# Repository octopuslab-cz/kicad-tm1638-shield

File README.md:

# kicad-tm1638-shield
display and keyboard shield for octopusLAB ESP32board

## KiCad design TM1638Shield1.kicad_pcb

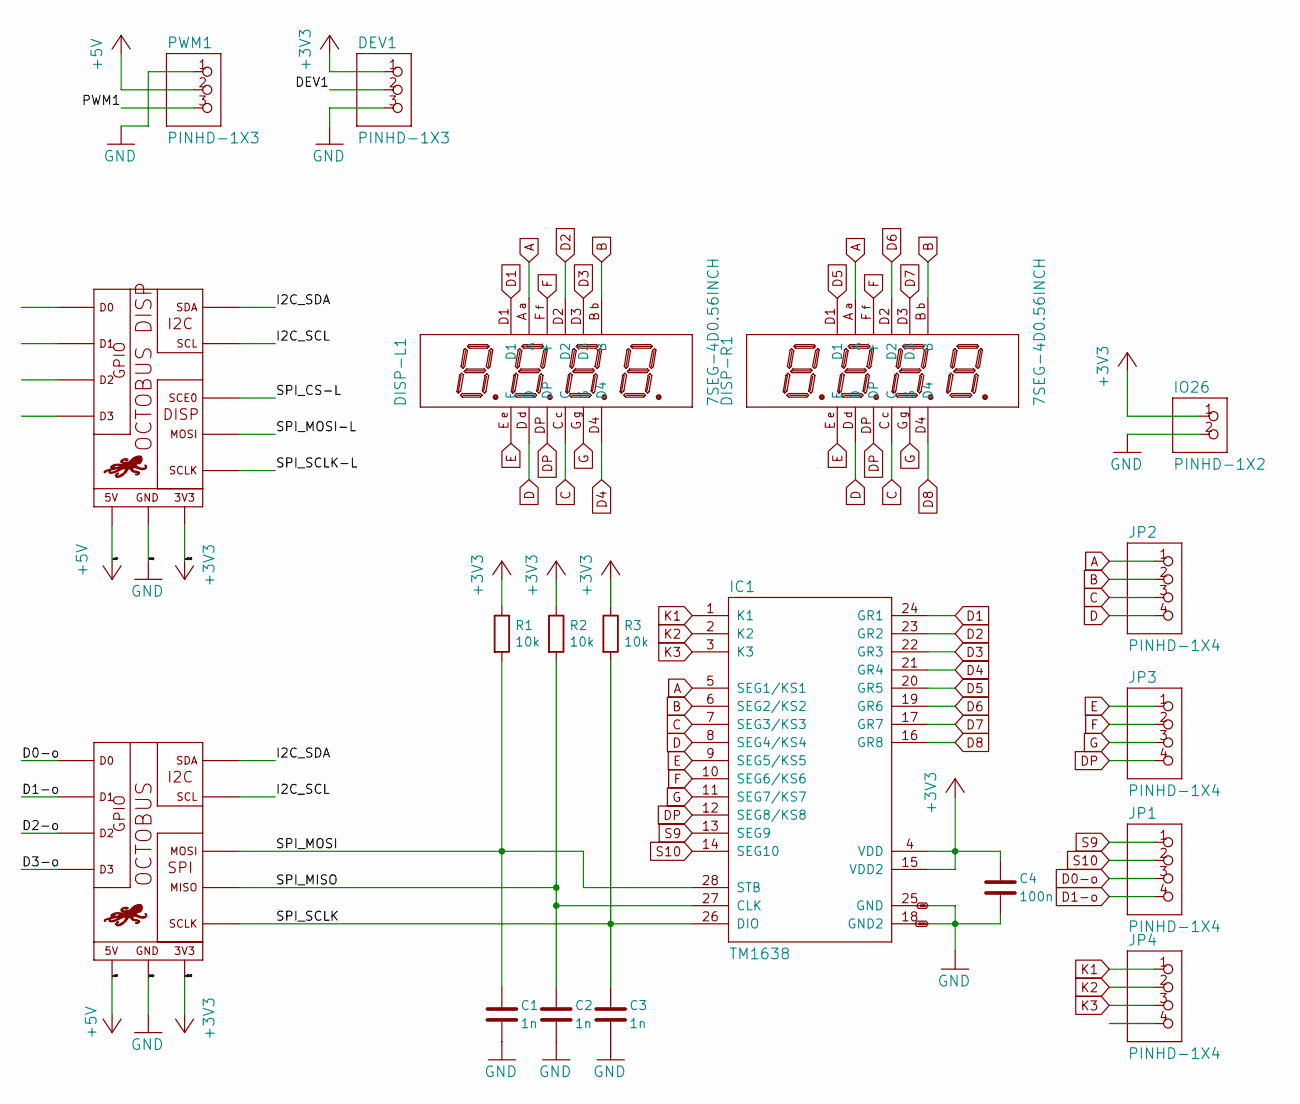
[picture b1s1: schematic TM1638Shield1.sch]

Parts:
C1, C2, C3: 1n; C_0805_2012Metric
C4: 100n; C_0805_2012Metric
DEV1: PINHD-1X3; 1X03
DISP-L1: 7SEG-4D0.56INCH; BQ-MB14RD
DISP-R1: 7SEG-4D0.56INCH; BQ-MB14RD
IC1: TM1638; SOP28
IO26: PINHD-1X2; 1X02
JP1, JP2, JP3, JP4: PINHD-1X4; 1X04
PWM1: PINHD-1X3; 1X03
R1, R2, R3: 10k; R_0805_2012Metric
U$1: OCTOBUSFULL; OCTOBUS
U$4: OCTOBUS_DISP

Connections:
+3V3: C4.1, DEV1.1, IC1.4 (VDD), IC1.15 (VDD2), IO26.1, R1.1, R2.1, R3.1, U$1.3V3, U$1.3V3_2 (3V3), U$1.3V3_AUX (3V3), U$4.3V3, U$4.3V3_2 (3V3)
+5V: PWM1.2, U$1.5V, U$1.5V_AUX (5V), U$4.5V
/D2-o: U$1.D2, U$1.D2_AUX (D2)
/D3-o: U$1.D3, U$1.D3_AUX (D3)
/DEV1: DEV1.2
/I2C_SCL: U$1.I2C_SCL (SCL), U$4.I2C_SCL (SCL)
/I2C_SDA: U$1.I2C_SDA (SDA), U$4.I2C_SDA (SDA)
/PWM1: PWM1.3
/SPI_CS-L: U$4.SPI_SCE0 (SCE0)
/SPI_MISO: C2.1, IC1.27 (CLK), R2.2, U$1.SPI_MISO (MISO)
/SPI_MOSI: C1.1, IC1.28 (STB), R1.2, U$1.SPI_MOSI (MOSI)
/SPI_MOSI-L: U$4.SPI_MOSI (MOSI)
/SPI_SCLK: C3.1, IC1.26 (DIO), R3.2, U$1.SPI_SCLK (SCLK)
/SPI_SCLK-L: U$4.SPI_SCLK (SCLK)
A: DISP-L1.A, DISP-R1.A, IC1.5 (SEG1/KS1), JP2.1
B: DISP-L1.B, DISP-R1.B, IC1.6 (SEG2/KS2), JP2.2
C: DISP-L1.C, DISP-R1.C, IC1.7 (SEG3/KS3), JP2.3
D: DISP-L1.D, DISP-R1.D, IC1.8 (SEG4/KS4), JP2.4
D0-o: JP1.3, U$1.D0, U$1.D0_AUX (D0)
D1: DISP-L1.D1, IC1.24 (GR1)
D1-o: JP1.4, U$1.D1, U$1.D1_AUX (D1)
D2: DISP-L1.D2, IC1.23 (GR2)
D3: DISP-L1.D3, IC1.22 (GR3)
D4: DISP-L1.D4, IC1.21 (GR4)
D5: DISP-R1.D1, IC1.20 (GR5)
D6: DISP-R1.D2, IC1.19 (GR6)
D7: DISP-R1.D3, IC1.17 (GR7)
D8: DISP-R1.D4, IC1.16 (GR8)
DP: DISP-L1.DP, DISP-R1.DP, IC1.12 (SEG8/KS8), JP3.4
E: DISP-L1.E, DISP-R1.E, IC1.9 (SEG5/KS5), JP3.1
F: DISP-L1.F, DISP-R1.F, IC1.10 (SEG6/KS6), JP3.2
G: DISP-L1.G, DISP-R1.G, IC1.11 (SEG7/KS7), JP3.3
GND: C1.2, C2.2, C3.2, C4.2, DEV1.3, IC1.18 (GND2), IC1.25 (GND), IO26.2, PWM1.1, U$1.GND, U$1.GND_2 (GND), U$1.GND_AUX (GND), U$4.GND, U$4.GND_2 (GND)
K1: IC1.1 (K1), JP4.1
K2: IC1.2 (K2), JP4.2
K3: IC1.3 (K3), JP4.3
S9: IC1.13 (SEG9), JP1.1
S10: IC1.14 (SEG10), JP1.2

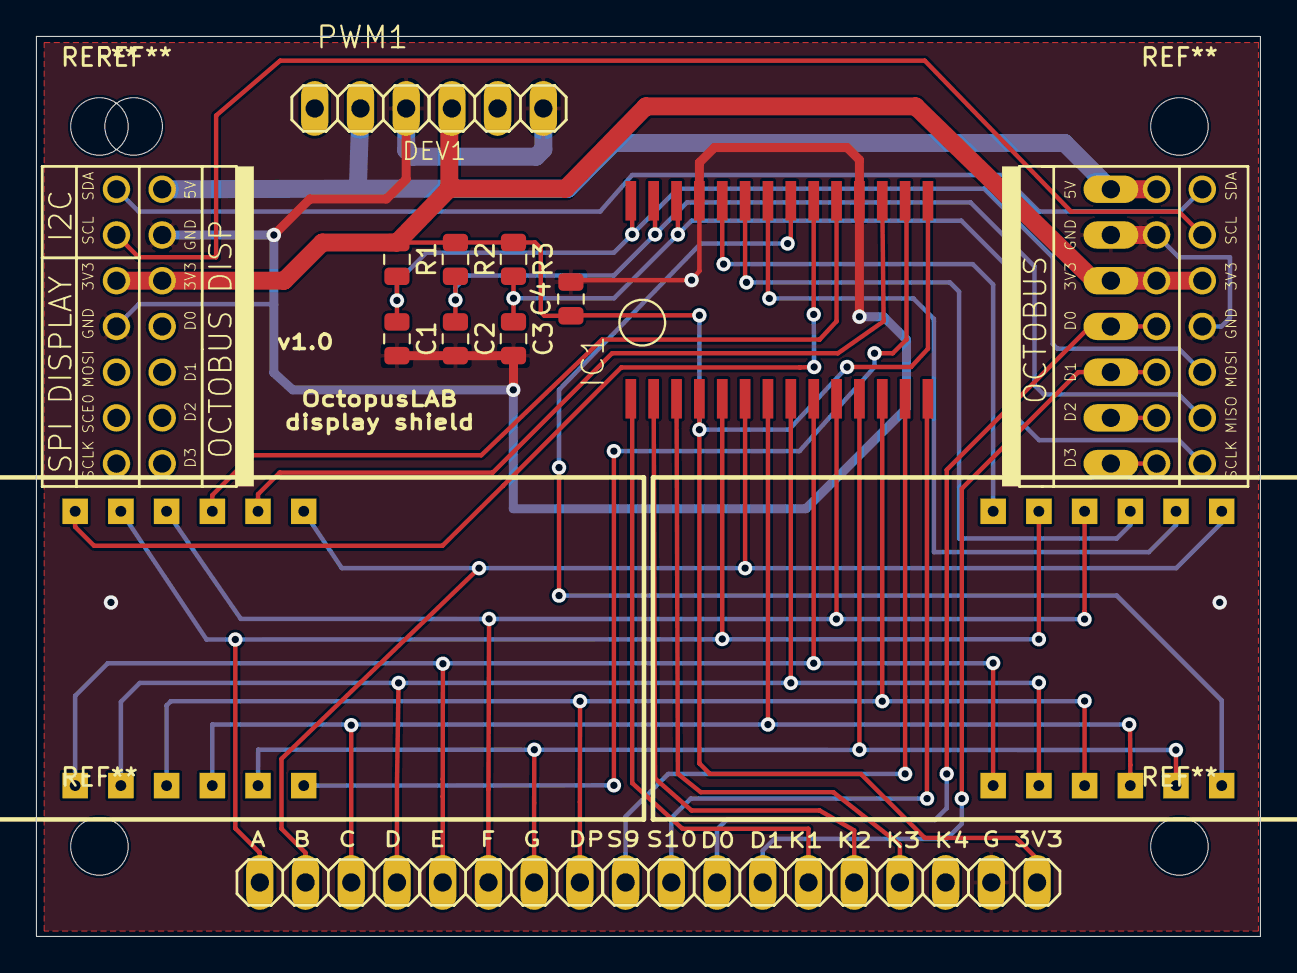
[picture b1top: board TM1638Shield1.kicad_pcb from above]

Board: 2 copper layers, 68.0 x 50.0 mm, 19 parts (0 on the bottom side), 33 nets.

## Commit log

2020-08-01 initial load
